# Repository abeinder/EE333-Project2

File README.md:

# EE333-Project2

This project contains the PCB design and software neccesary to run a custom made BLDC and servo controller. The controller also interfaces with an LCD and communicates to a python app run on a PC over Bluetooth using the BLE interface. It was created for the EE333 PCB design course at Iowa State.

The controller uses the Atmega 2560 chip for all purposes. The BLDC controller was inspired by a blog post (https://simple-circuit.com/arduino-sensorless-bldc-motor-controller-esc/) and converted from being for the Atmega 328 to the 2560. The bluetooth utilizes the AT09 breakout board.

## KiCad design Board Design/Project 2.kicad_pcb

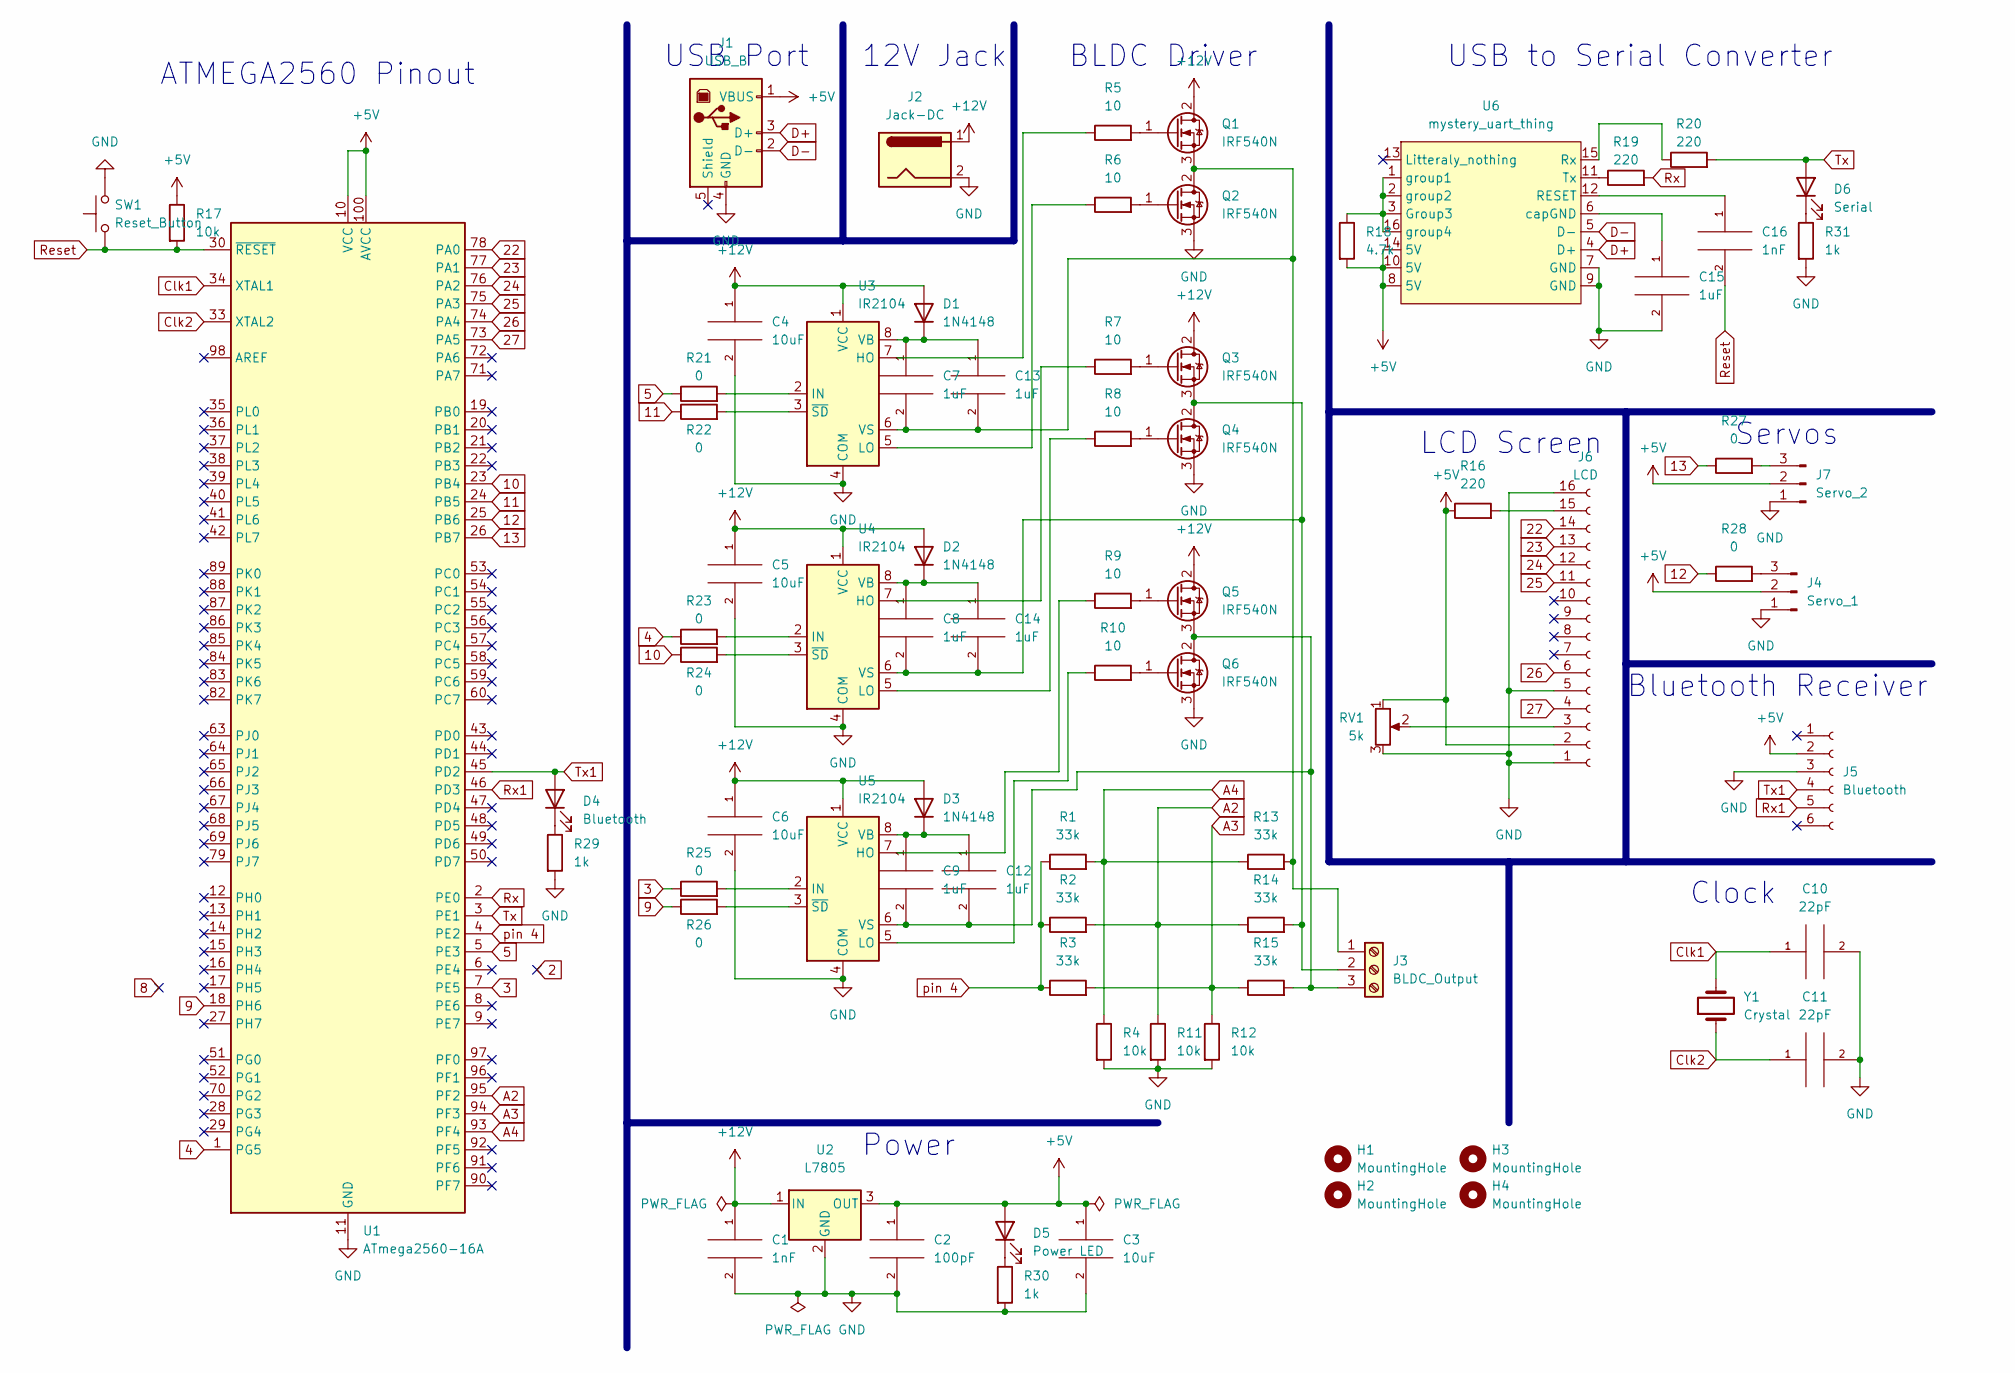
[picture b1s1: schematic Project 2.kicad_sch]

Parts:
C1, C16: 1nF; C_Disc_D3.0mm_W2.0mm_P2.50mm
C2: 100pF; C_Disc_D3.0mm_W2.0mm_P2.50mm
C3, C4, C5, C6: 10uF; C_Radial_D5.0mm_H11.0mm_P2.00mm
C7, C8, C9, C12, C13, C14, C15: 1uF; C_Radial_D5.0mm_H11.0mm_P2.00mm
C10, C11: 22pF; C_Disc_D3.0mm_W2.0mm_P2.50mm
D1, D2, D3: 1N4148; D_DO-35_SOD27_P7.62mm_Horizontal
D4: Bluetooth; LED_D3.0mm
D5: Power LED; LED_D3.0mm
D6: Serial; LED_D3.0mm
H1, H2, H3, H4: MountingHole; MountingHole_5mm_Pad
J1: USB_B; USB_B_Lumberg_2411_02_Horizontal
J2: Jack-DC; BarrelJack_GCT_DCJ200-10-A_Horizontal
J3: BLDC_Output; PinSocket_1x03_P2.54mm_Vertical
J4: Servo_1; PinHeader_1x03_P2.54mm_Vertical
J5: Bluetooth; PinSocket_1x06_P2.54mm_Vertical
J6: LCD; WC1602A
J7: Servo_2; PinHeader_1x03_P2.54mm_Vertical
Q1, Q2, Q3, Q4, Q5, Q6: IRF540N; TO-220-3_Vertical
R1, R2, R3, R13, R14, R15: 33k; R_Axial_DIN0207_L6.3mm_D2.5mm_P7.62mm_Horizontal
R4, R11, R12, R17: 10k; R_Axial_DIN0207_L6.3mm_D2.5mm_P7.62mm_Horizontal
R5, R6, R7, R8, R9, R10: 10; R_Axial_DIN0207_L6.3mm_D2.5mm_P7.62mm_Horizontal
R16, R19, R20: 220; R_Axial_DIN0207_L6.3mm_D2.5mm_P7.62mm_Horizontal
R18: 4.7k; R_Axial_DIN0207_L6.3mm_D2.5mm_P7.62mm_Horizontal
R21, R22, R23, R24, R25, R26, R27, R28: 0; R_Axial_DIN0207_L6.3mm_D2.5mm_P7.62mm_Horizontal
R29, R30, R31: 1k; R_Axial_DIN0207_L6.3mm_D2.5mm_P7.62mm_Horizontal
RV1: 5k; Potentiometer_Bourns_3386P_Vertical
SW1: Reset_Button; SW_PUSH_6mm_H4.3mm
U1: ATmega2560-16A; ATMEGA2560_breakout_Board_Socket
U2: L7805; TO-220-3_Vertical
U3, U4, U5: IR2104; SOIC-8_3.9x4.9mm_P1.27mm
U6: mystery_uart_thing; SOP-16_3.9x9.9mm_P1.27mm
Y1: Crystal; Crystal_AT310_D3.0mm_L10.0mm_Vertical

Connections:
3: R25.1, U1.7 (PE5)
4: R23.1, U1.1 (PG5)
5: R21.1, U1.5 (PE3)
9: R26.1, U1.18 (PH6)
10: R24.1, U1.23 (PB4)
11: R22.1, U1.24 (PB5)
12: R28.1, U1.25 (PB6)
13: R27.1, U1.26 (PB7)
22: J6.14, U1.78 (PA0)
23: J6.13, U1.77 (PA1)
24: J6.12, U1.76 (PA2)
25: J6.11, U1.75 (PA3)
26: J6.6, U1.74 (PA4)
27: J6.4, U1.73 (PA5)
+5V: C2.1, C3.1, D5.2 (A), J1.1 (VBUS), J4.2, J5.2, J6.2, J7.2, R16.1, R17.1, R18.2, RV1.1, U1.10 (VCC), U1.31 (VCC), U1.61 (VCC), U1.80 (VCC), U1.100 (AVCC), U2.3 (OUT), U6.8 (5V), U6.10 (5V), U6.14 (5V)
+12V: C1.1, C4.1, C5.1, C6.1, D1.2 (A), D2.2 (A), D3.2 (A), J2.1, Q1.2 (D), Q3.2 (D), Q5.2 (D), U2.1 (IN), U3.1 (VCC), U4.1 (VCC), U5.1 (VCC)
A2: R2.2, R11.1, R14.1, U1.95 (PF2)
A3: R3.2, R12.1, R15.1, U1.94 (PF3)
A4: R1.2, R4.1, R13.1, U1.93 (PF4)
Clk1: C10.1, U1.34 (XTAL1), Y1.2
Clk2: C11.1, U1.33 (XTAL2), Y1.1
D+: J1.3 (D+), U6.4 (D+)
D-: J1.2 (D-), U6.5 (D-)
GND: C1.2, C2.2, C3.2, C4.2, C5.2, C6.2, C10.2, C11.2, C15.2, H1.1, H2.1, H3.1, H4.1, J1.4 (GND), J2.2, J4.1, J5.3, J6.1, J6.5, J6.16, J7.1, Q2.3 (S), Q4.3 (S), Q6.3 (S), R4.2, R11.2, R12.2, R29.2, R30.2, R31.2, RV1.3, SW1.2, U1.11 (GND), U1.32 (GND), U1.62 (GND), U1.81 (GND), U1.99 (GND), U2.2 (GND), U3.4 (COM), U4.4 (COM), U5.4 (COM), U6.7 (GND), U6.9 (GND)
unnamed: C9.1, C12.1, D3.1 (K), U5.8 (VB)
unnamed: C9.2, C12.2, J3.3, Q5.3 (S), Q6.2 (D), R15.2, U5.6 (VS)
unnamed: C7.1, C13.1, D1.1 (K), U3.8 (VB)
unnamed: C7.2, C13.2, J3.1, Q1.3 (S), Q2.2 (D), R13.2, U3.6 (VS)
unnamed: C8.1, C14.1, D2.1 (K), U4.8 (VB)
unnamed: C8.2, C14.2, J3.2, Q3.3 (S), Q4.2 (D), R14.2, U4.6 (VS)
unnamed: C15.1, U6.6 (capGND)
unnamed: C16.1, U6.12 (RESET)
unnamed: D4.1 (K), R29.1
unnamed: D5.1 (K), R30.1
unnamed: D6.1 (K), R31.1
unnamed: J4.3, R28.2
unnamed: J6.3, RV1.2
unnamed: J6.15, R16.2
unnamed: J7.3, R27.2
unnamed: Q1.1 (G), R5.2
unnamed: Q2.1 (G), R6.2
unnamed: Q3.1 (G), R7.2
unnamed: Q4.1 (G), R8.2
unnamed: Q5.1 (G), R9.2
unnamed: Q6.1 (G), R10.2
unnamed: R5.1, U3.7 (HO)
unnamed: R6.1, U3.5 (LO)
unnamed: R7.1, U4.7 (HO)
unnamed: R8.1, U4.5 (LO)
unnamed: R9.1, U5.7 (HO)
unnamed: R10.1, U5.5 (LO)
unnamed: R18.1, U6.1 (group1), U6.2 (group2), U6.3 (Group3), U6.16 (group4)
unnamed: R19.1, U6.11 (Tx)
unnamed: R20.1, U6.15 (Rx)
unnamed: R21.2, U3.2 (IN)
unnamed: R22.2, U3.3 (~SD)
unnamed: R23.2, U4.2 (IN)
unnamed: R24.2, U4.3 (~SD)
unnamed: R25.2, U5.2 (IN)
unnamed: R26.2, U5.3 (~SD)
Reset: C16.2, R17.2, SW1.1, U1.30 (~RESET)
Rx: R19.2, U1.2 (PE0)
Rx1: J5.5, U1.46 (PD3)
Tx: D6.2 (A), R20.2, U1.3 (PE1)
Tx1: D4.2 (A), J5.4, U1.45 (PD2)
pin 4: R1.1, R2.1, R3.1, U1.4 (PE2)

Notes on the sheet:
Clock
12V Jack
USB to Serial Converter
Power
Servos
USB Port
ATMEGA2560 Pinout
LCD Screen
Bluetooth Receiver
BLDC Driver

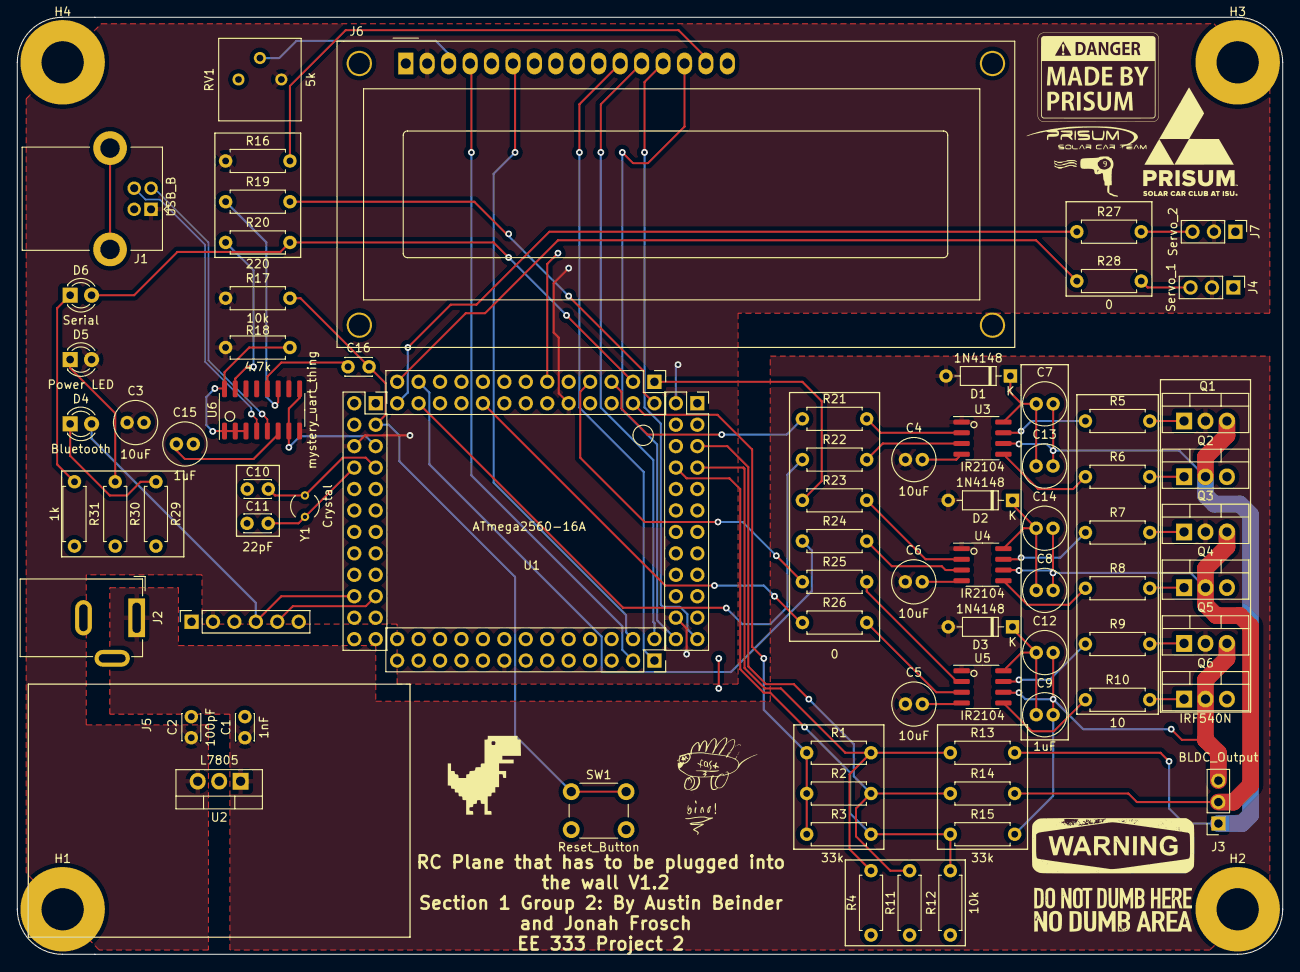
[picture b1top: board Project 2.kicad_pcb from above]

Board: 2 copper layers, 149.9 x 111.0 mm, 79 parts (0 on the bottom side), 66 nets.

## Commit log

2022-10-24 added kicad files
2022-10-29 added ATMEDA2560 breakout board footprint
2022-11-08 initial PCB design
2022-11-12 added all sw to the repo
2022-12-03 added current pcb
2022-12-03 all changes
2022-12-03 any and all
2022-12-10 removed Project2
2022-12-10 renamed so things were clearer
2022-12-10 added better documentation for python files
2022-12-10 adding report
